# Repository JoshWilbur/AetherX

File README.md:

# AetherX

AetherX is a precision environmental sensor which can gather a number of statistics in real time. This device was designed with ease of use and portability in mind. This project is in a functional state and is considered "complete" for the time being. All features of this project, minus the microphone, are functional and calibrated. In the future, I plan to revisit this project to make improvements.

All code for this project is within Core/src. Schematic, PCB and assembly files are contained within AetherX_KiCad.

**Sensors:**

* LM61 - Temperature
* DHT20 - Relative humidity and temperature
* OPT101 - Light intensity at 650nm wavelength
* MAX9814 - Microphone with signal output

**Power**

This device is powered by 2x AA batteries. I tested the battery life of this device and found it can last ~1 month before a battery change is needed. Further improvements could be made to the code for additional power savings.

* 2/25/25: 5mA @ 3V (15mW)
* 7/30/25  3.8mA @ 3V (11.4mW)

# TODO:

**Software**

* Re-do reading functions with ADC rank (only do readings when displayed)
* Screens: ADC voltage stats, humidity, time/date, clicker, settings?
* Restructure data in structs?
* Signal processing for MAX9814 (frequency data via FFT, sound level in dB)

**Future Work**

* Wireless daughter boards (STM32WB55, 3D print sphere case?)
* Data logging (>24hrs)

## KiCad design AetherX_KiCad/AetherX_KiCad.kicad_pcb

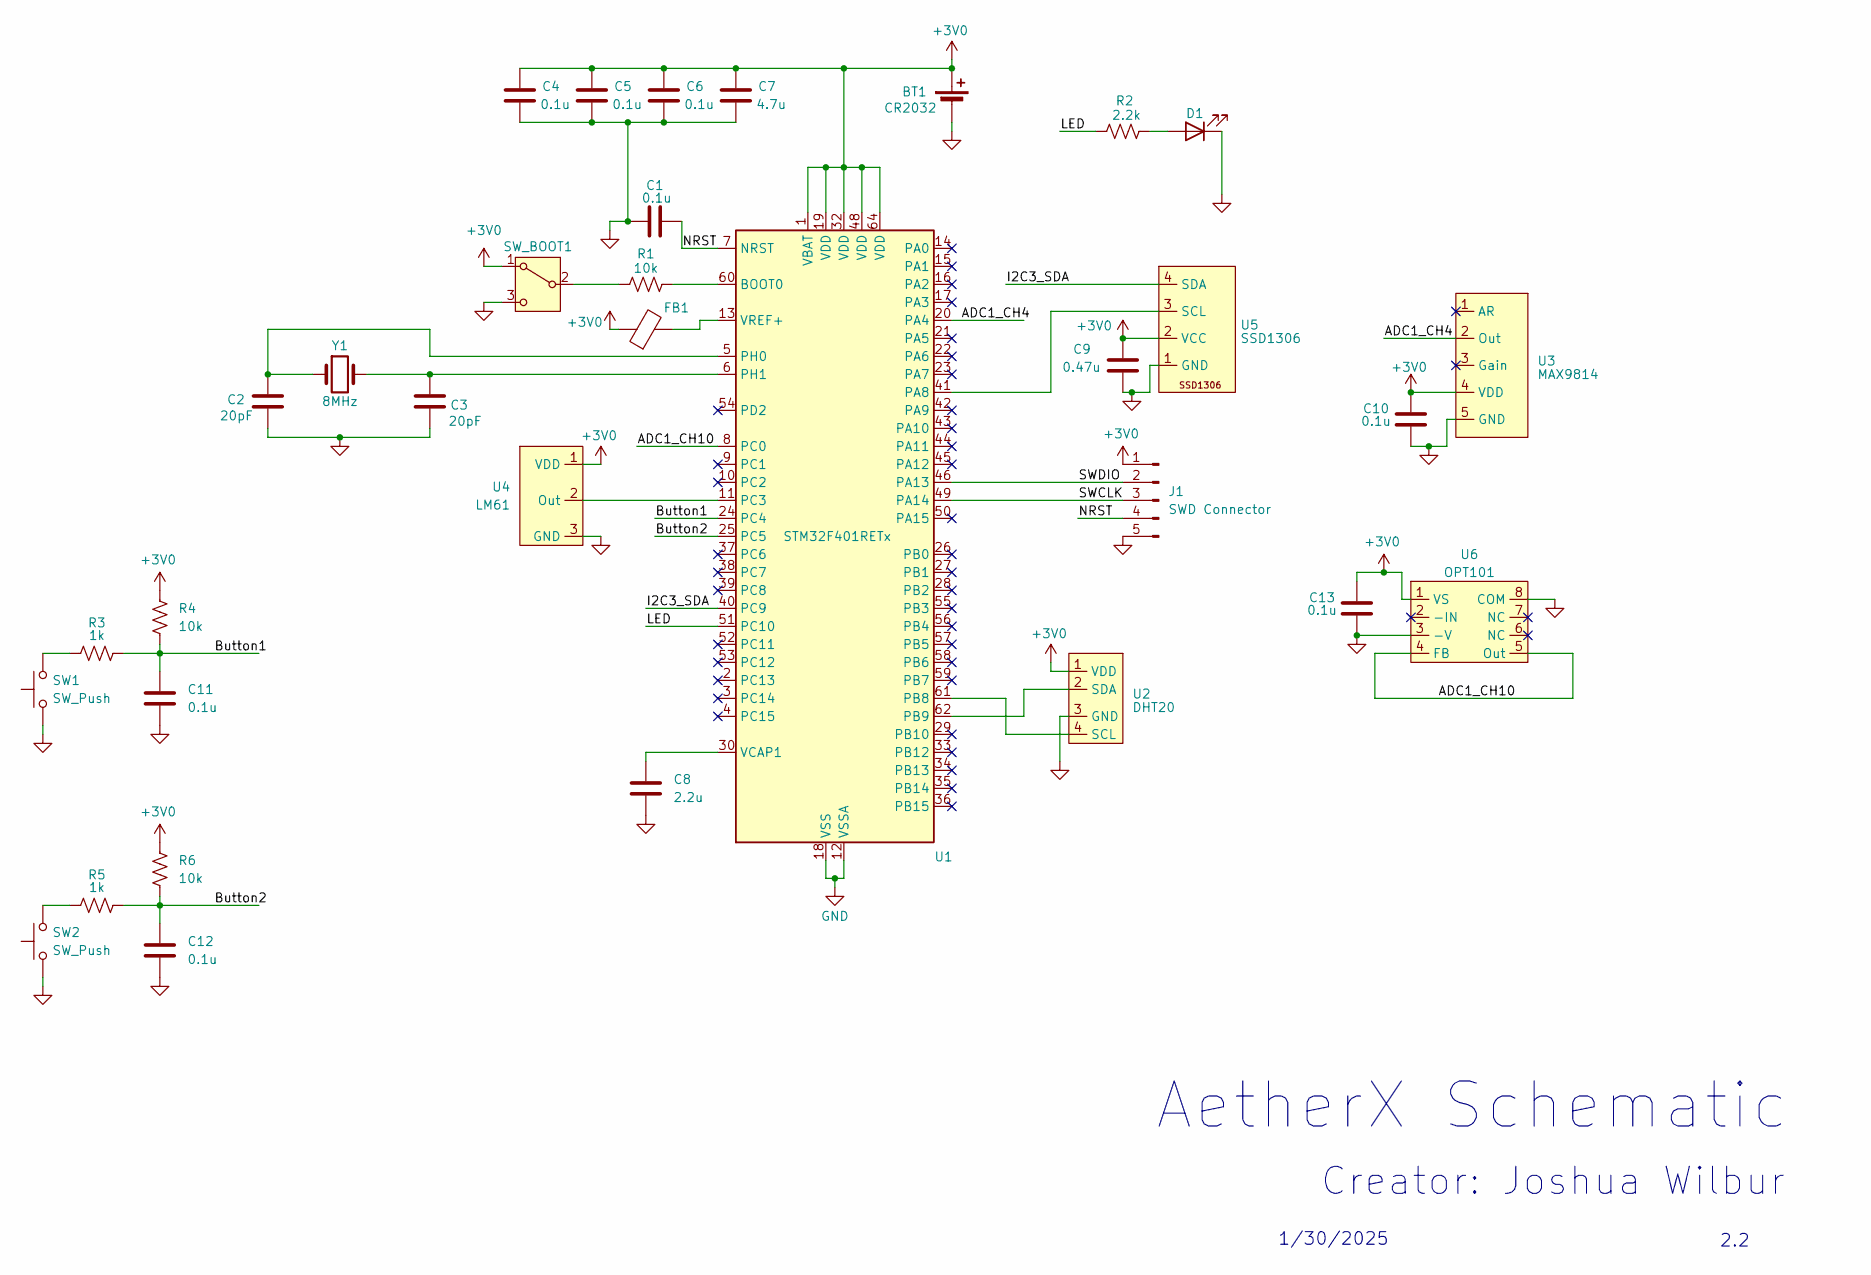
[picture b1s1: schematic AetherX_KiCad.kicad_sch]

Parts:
BT1: CR2032; BatteryHolder_Keystone_103_1x20mm
C1: 0.1u; C_Disc_D5.1mm_W3.2mm_P5.00mm
C2, C3: 20pF; C_Disc_D5.1mm_W3.2mm_P5.00mm
C4, C5, C6, C10, C11, C12, C13: 0.1u; C_0402_1005Metric_Pad0.74x0.62mm_HandSolder
C7: 4.7u; C_0805_2012Metric_Pad1.18x1.45mm_HandSolder
C8: 2.2u; C_Disc_D5.1mm_W3.2mm_P5.00mm
C9: 0.47u; C_Disc_D5.1mm_W3.2mm_P5.00mm
D1: LED; LED_D5.0mm
FB1: FerriteBead; L_Axial_L7.0mm_D3.3mm_P12.70mm_Horizontal_Fastron_MICC
J1: SWD Connector; PinSocket_1x05_P2.54mm_Vertical
R1, R4, R6: 10k; R_Axial_DIN0207_L6.3mm_D2.5mm_P10.16mm_Horizontal
R2: 2.2k; R_Axial_DIN0207_L6.3mm_D2.5mm_P10.16mm_Horizontal
R3, R5: 1k; R_Axial_DIN0207_L6.3mm_D2.5mm_P10.16mm_Horizontal
SW1, SW2: SW_Push; SW_PUSH_1P1T_6x3.5mm_H5.0_APEM_MJTP1250
SW_BOOT1: SW_SPDT; PinHeader_1x03_P2.54mm_Vertical
U1: STM32F401RETx; LQFP-64_10x10mm_P0.5mm
U2: DHT20; PinSocket_1x04_P2.54mm_Vertical
U3: MAX9814; PinSocket_1x05_P2.54mm_Vertical
U4: LM61; PinHeader_1x03_P2.54mm_Vertical
U5: SSD1306; PinSocket_1x04_P2.54mm_Vertical
U6: OPT101; DIP-8_W7.62mm
Y1: 8MHz; Crystal_HC49-4H_Vertical

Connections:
+3V0: BT1.1 (+), C4.1, C5.1, C6.1, C7.1, C9.1, C10.1, C13.1, FB1.1, J1.1, R4.1, R6.1, SW_BOOT1.1 (A), U1.1 (VBAT), U1.19 (VDD), U1.32 (VDD), U1.48 (VDD), U1.64 (VDD), U2.1 (VDD), U3.4 (VDD), U4.1 (VDD), U5.2 (VCC), U6.1 (VS); also elsewhere on the board
/ADC1_CH4: U1.20 (PA4), U3.2 (Out)
/ADC1_CH10: U1.8 (PC0), U6.4 (FB), U6.5 (Out)
/Button1: C11.1, R3.2, R4.2, U1.24 (PC4)
/Button2: C12.1, R5.2, R6.2, U1.25 (PC5)
/I2C3_SDA: U1.40 (PC9), U5.4 (SDA)
/LED: R2.1, U1.51 (PC10)
/NRST: C1.2, J1.4, U1.7 (NRST); also elsewhere on the board
/SWCLK: J1.3, U1.49 (PA14); also elsewhere on the board
/SWDIO: J1.2, U1.46 (PA13); also elsewhere on the board
GND: BT1.2 (-), C1.1, C2.2, C3.2, C4.2, C5.2, C6.2, C7.2, C8.2, C9.2, C10.2, C11.2, C12.2, C13.2, D1.1 (K), J1.5, SW1.1, SW2.1, SW_BOOT1.3 (C), U1.12 (VSSA), U1.18 (VSS), U1.31 (VSS), U1.47 (VSS), U1.63 (VSS), U2.3 (GND), U3.5 (GND), U4.3 (GND), U5.1 (GND), U6.3 (-V), U6.8 (COM); also elsewhere on the board
unnamed: D1.2 (A), R2.2
unnamed: R3.1, SW1.2
unnamed: R5.1, SW2.2
unnamed: R1.1, SW_BOOT1.2 (B)
unnamed: R1.2, U1.60 (BOOT0)
unnamed: U1.41 (PA8), U5.3 (SCL)
unnamed: U1.61 (PB8), U2.4 (SCL)
unnamed: U1.62 (PB9), U2.2 (SDA)
unnamed: U1.11 (PC3), U4.2 (Out)
unnamed: C2.1, U1.5 (PH0), Y1.1
unnamed: C3.1, U1.6 (PH1), Y1.2
unnamed: C8.1, U1.30 (VCAP1)
unnamed: FB1.2, U1.13 (VREF+)

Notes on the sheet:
AetherX Schematic
2.2
Creator: Joshua Wilbur
1/30/2025

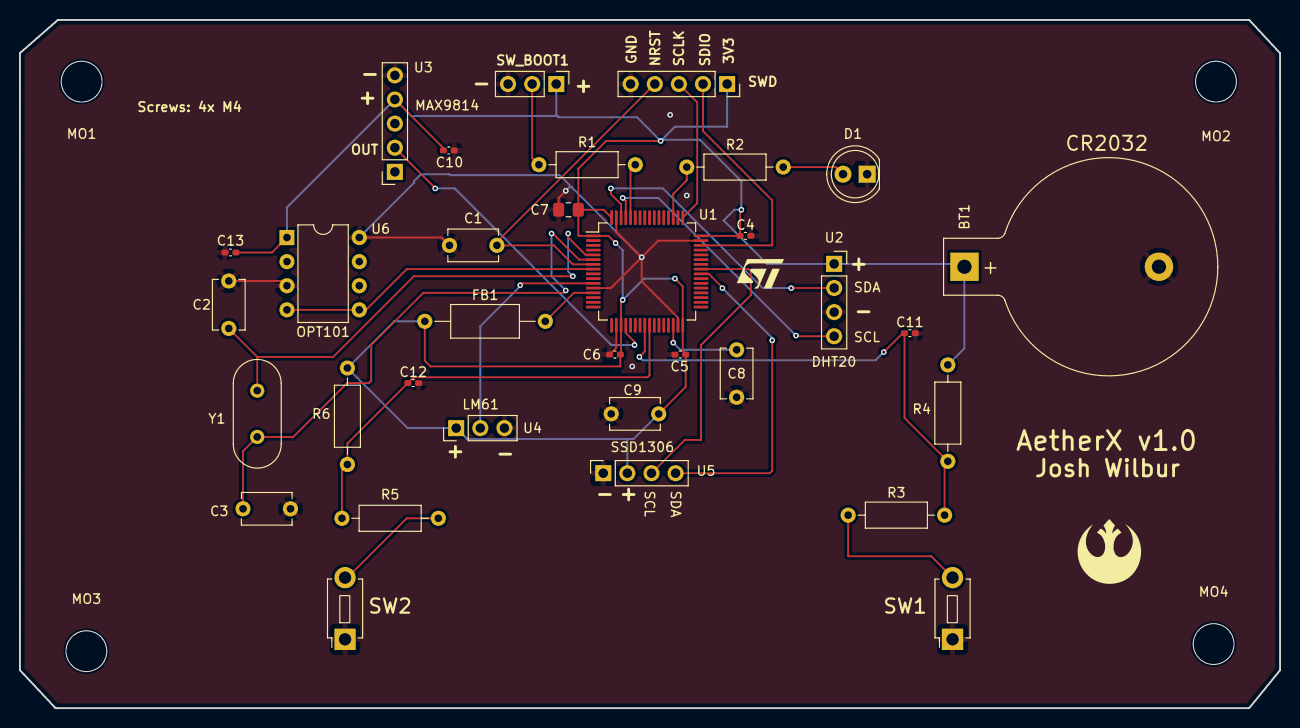
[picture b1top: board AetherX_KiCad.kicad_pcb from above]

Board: 2 copper layers, 132.8 x 72.5 mm, 37 parts (0 on the bottom side), 24 nets.

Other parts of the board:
MO1, MO2, MO3, MO4: MountingHole_4.3mm_M4
SWD: SWD Connector; PinSocket_1x05_P2.54mm_Vertical

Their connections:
+3V0: SWD.1; also elsewhere on the board
/NRST: SWD.4; also elsewhere on the board
/SWCLK: SWD.3; also elsewhere on the board
/SWDIO: SWD.2; also elsewhere on the board
GND: SWD.5; also elsewhere on the board

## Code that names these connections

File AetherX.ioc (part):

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Mcu.Name=STM32F401R(D-E)Tx
Mcu.Package=LQFP64
Mcu.UserName=STM32F401RETx
PA13.Mode=Trace_Asynchronous_SW
PA13.Signal=SYS_JTMS-SWDIO
PA14.Mode=Trace_Asynchronous_SW
PA14.Signal=SYS_JTCK-SWCLK
PA4.Signal=ADCx_IN4
PA8.Mode=I2C
PA8.Signal=I2C3_SCL
PB3.Mode=Trace_Asynchronous_SW
PB3.Signal=SYS_JTDO-SWO
PB8.Mode=I2C
PB8.Signal=I2C1_SCL
PB9.Mode=I2C
PB9.Signal=I2C1_SDA
PC0.Signal=ADCx_IN10
PC10.GPIOParameters=GPIO_Speed
PC10.GPIO_Speed=GPIO_SPEED_FREQ_LOW
PC10.Signal=GPIO_Output
PC3.Signal=ADCx_IN13
PC4.Signal=GPIO_Input
PC5.Signal=GPIO_Input
PC9.Mode=I2C
PC9.Signal=I2C3_SDA
RCC.HSE_VALUE=25000000
RCC.SYSCLKFreq_VALUE=16000000
board=custom

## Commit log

2024-12-24 add STM32 project files
2024-12-24 created gitignore
2024-12-25 begin mpl3115a2 functions
2024-12-25 i2c working with the altmeter
2024-12-27 further debugged the barometer, still getting incorrect vals
2024-12-30 LM61 temp sensor code written, device works great
2024-12-31 OPT101 sensor code written, calibration needed
2025-01-01 DHT20 sensor code written
2025-01-03 MAX9814 mic set up
2025-01-03 DMA is working for the mic! signal processing can now begin
2025-01-03 begin KiCad schematic for Aether
2025-01-03 set up internal RTC
2025-01-07 ssd1306 display is talking, static output though
2025-01-16 OLED display is working good, but need to adjust offset
2025-01-19 readings shown on OLED display
2025-01-19 update schematic
2025-01-25 user input code
2025-01-25 internal ADC VRef code added
2025-01-30 schematic V2 complete
2025-02-07 first PCB complete
2025-02-09 PCB ordered, uploaded BOM and gerber files
2025-02-24 schematic v3 uploaded
2025-02-24 various code improvements: opt101, LED, input interrupts, screens...
2025-02-24 Test push from laptop
2025-02-24 update readings to use a timer interrupt
2025-02-25 fixed ADC internal voltage, now displayed on readings screen
2025-02-25 speed up readings and optimize main loop
2025-03-14 add standby mode
2025-03-18 stop mode and wake up implemented
2025-03-19 De-init peripherals when entering STOP mode, rewrote average functions
2025-03-21 RTC working
2025-04-18 battery test complete, 26 days on 2x AA batteries
2025-05-19 refactor functions for less future pain
2025-05-20 finally fixed display, added high/low stats
2025-05-20 cleanup after fixing display
2025-07-13 upload aetherx image to readme
2025-07-30 final update for a while
